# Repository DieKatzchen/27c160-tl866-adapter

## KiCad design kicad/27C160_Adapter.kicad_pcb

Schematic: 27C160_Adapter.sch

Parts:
Q1: BC327; TO92-EBC
R1, R2, R3, R4, R5: 10k; 0207_10
SW1: MS22D16
SW2: 94HBB08T
U1: 27C4002
ZX1: 3M_248-3345

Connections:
/A0: U1.21 (A0), ZX1.13
/A1: U1.22 (A1), ZX1.12
/A2: U1.23 (A2), ZX1.11
/A3: U1.24 (A3), ZX1.10
/A4: U1.25 (A4), ZX1.9
/A5: U1.26 (A5), ZX1.8
/A6: U1.27 (A6), ZX1.7
/A7: U1.28 (A7), ZX1.6
/A8: U1.29 (A8), ZX1.44
/A9: U1.31 (A9), ZX1.43
/A10: U1.32 (A10), ZX1.42
/A11: U1.33 (A11), ZX1.41
/A12: U1.34 (A12), ZX1.40
/A13: U1.35 (A13), ZX1.39
/A14: U1.36 (A14), ZX1.38
/A15: U1.37 (A15), ZX1.37
/A16: U1.38 (A16), ZX1.36
/A17: U1.39 (A17), ZX1.5
/A18: R3.1, SW2.1, ZX1.4
/A19: R2.1, SW2.2, ZX1.45
/A20: R1.1, SW1.3 (S), SW2.4
/D0: U1.19 (D0), ZX1.17
/D1: U1.18 (D1), ZX1.19
/D2: U1.17 (D2), ZX1.21
/D3: U1.16 (D3), ZX1.23
/D4: U1.15 (D4), ZX1.26
/D5: U1.14 (D5), ZX1.28
/D6: U1.13 (D6), ZX1.30
/D7: U1.12 (D7), ZX1.32
/D8: U1.10 (D8), ZX1.18
/D9: U1.9 (D9), ZX1.20
/D10: U1.8 (D10), ZX1.22
/D11: U1.7 (D11), ZX1.24
/D12: U1.6 (D12), ZX1.27
/D13: U1.5 (D13), ZX1.29
/D14: U1.4 (D14), ZX1.31
/D15: U1.3 (D15), ZX1.33
/E: U1.2 (/CE), ZX1.14
/N$1: Q1.B, R5.2
/N$2: SW1.2, ZX1.35
/N$4: Q1.C, R4.2, SW1.6 (S1)
/N$5: SW1.4 (O1), U1.20 (/G)
/N$6: SW1.5 (P1), ZX1.16
/VPP: Q1.E, SW1.1 (O), U1.1 (VPP)
GND: R1.2, R2.2, R3.2, R4.1, U1.11 (GND), U1.30 (GND), ZX1.15, ZX1.34
VCC: R5.1, SW2.C, U1.40 (VCC), ZX1.25

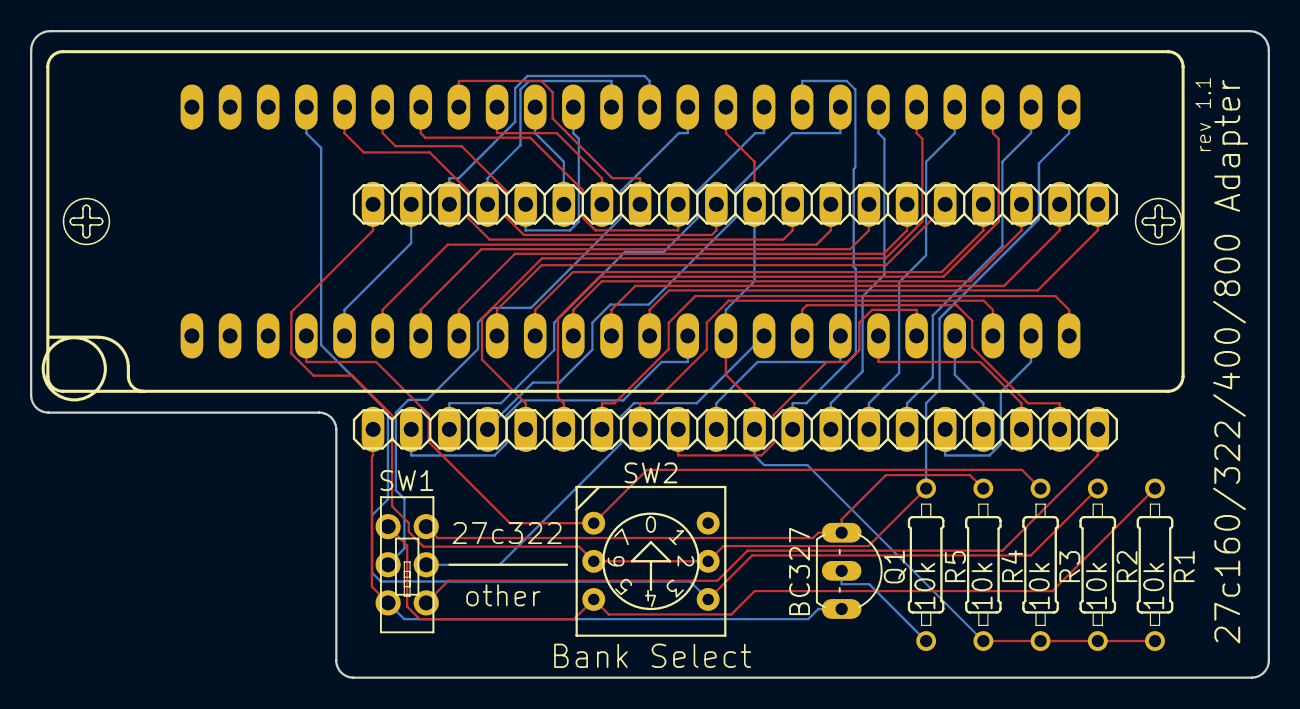
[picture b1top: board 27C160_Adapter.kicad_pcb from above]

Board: 2 copper layers, 82.4 x 43.1 mm, 10 parts (0 on the bottom side), 46 nets.

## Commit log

2018-06-10 Changed dip switch to coded rotary switch. Still needs rerouting.
2018-06-10 Version 1.1
    Changed dip switch to octal coded rotary switch, changed pullups to
    pulldowns to work with octal coded rotary switch, rerouted whole board
    and fiddled with silkscreen a bit. Fingers crossed I didn't mess it up.
2018-06-10 Hotfix for LSB error
    Whoops! had my LSB and MSB swapped. That would have given some undesired
    behavior.
2018-06-10 Gerbers
    Rebuilt the gerbers
2018-06-26 Actual fix for LSB/MSB mixup
    Had actually only rearranged the pulldown resistors. Which doesn't
    actually do anything at all. Let this be a lesson: if you make a
    correction at 2AM, check it before you send it to the fab house. Fixes
    Issue #1 .
2019-08-03 Rebuilt Gerbers, Panelized
    Pretty sure I never rebuilt the gerbers after fixing the LSB/MSB mixup. Now I have. Also panelized them.
